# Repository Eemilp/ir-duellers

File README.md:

# IR-duellers

Toy guns for a western-style duelling game. The pair of guns have an ir-LED and sensor each and can thus determine who shot first. When a gun "dies" it is not able to shoot anymore and has to be reset from a button to be functional again. 

A few images of the finished product: https://imgur.com/a/vaQRZun

## Electronics

The heart of the gun is an ATtiny85 with a TSOP312xx (TSOP31236 in this implementation) IR-receiver and an IR-LED. Additionally a status LED and a piezo-buzzer were added for feedback. 

A transistor was also added to amplify the IR-LEDs signal, but in hindsight this was unneccessary. The pizeo-buzzer could however have really done with some amplification, because it can be a bit too quiet sometimes. 

While operational everything runs on two AA batteries, but the design is 5v tolerant for programming purposes.  

The pcb also provides some breakout points for easier programming (VCC, GND, Reset, RX, TX). Unfotunately the internal clockspeed on the ATtiny85 seems to vary so much from chip to chip that it makes programming the chip over serial a hit or miss. Some chips seemed to work perfectly, while others just would not work. Therefore the chips were programmed with SPI. 

## Case

The case was designed in FreeCAD and 3d printed using PLA-plastic. Most parts are attached with screws but the trigger button is just slid in and held in place with friction. Note that the attachment of the top cover is not perfect and I have therefore used tape for fastening it as it's easier. 

The reset switch is a generic closing switch with a 7mm shaft. The trigger is a PS507MA, which is also a closing switch with a 16mm shaft.

------

## Software

Originally the program was written in the Arduino language. While this worked, an improved version was written in assembler. I have also included the version written in the Arduino language here, but be aware that it tends to be somewhat unreliable. Both versions here are programmed to work with 36kHz IR signal. 

Note that this project requires the ATTinyCore by SpenceKonde to be installed from the Arduino boards manager.

## Flashing the chips

The original plan was to program the chip over serial with the Arduino bootloader. This however did not appear to be reliable so programming the chips over SPI on a breadboard was used instead. An Arduino Uno (Arduino as ISP) was used as the programmer.

For the version written in assembler the hex file was generated with Atmel Studio and progamming was done with Avrdude. Avrdude comes with Arduino IDE and can be accessed over command line.

```bash

avrdude -CC:"\Path\to\Arduino\hardware\tools\avr/etc/avrdude.conf" -v -pattiny85 -carduino -PCOM3 -b19200 -U lfuse:w:0xE2:m -U hfuse:w:0xDF:m -U efuse:w:0xFF:m -Uflash:w:lightguns_asm_v1.hex:i

```

I have here the Arduino running Arduino as ISP on COM3. Also note the fuse settings. These set the internal oscillator at 8MHz and make sure that the chip can be programmed again using SPI.

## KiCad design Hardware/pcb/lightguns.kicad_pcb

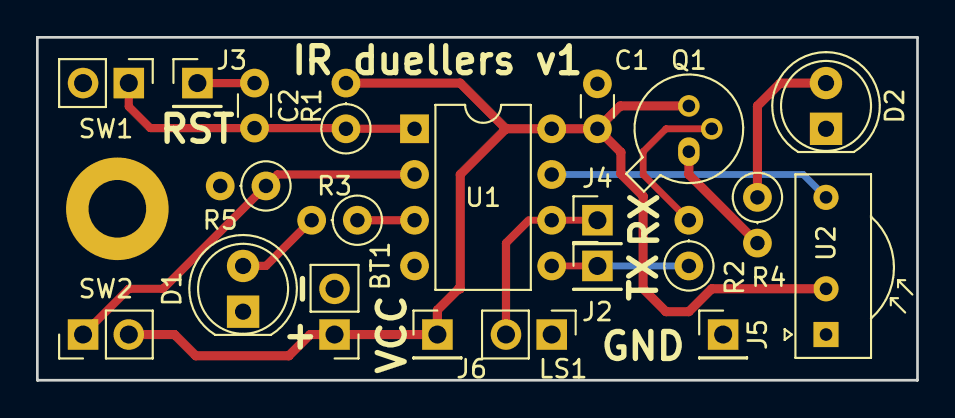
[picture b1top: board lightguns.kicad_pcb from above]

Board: 2 copper layers, 48.9 x 19.1 mm, 21 parts (0 on the bottom side), 13 nets.

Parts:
BT1: Battery; PinHeader_1x02_P2.54mm_Vertical
C1, C2: 0.1uF; C_Disc_D3.0mm_W1.6mm_P2.50mm
D1: LED; LED_D5.0mm_Clear
D2: IR_LED; LED_D5.0mm_IRGrey
J2: TX; PinHeader_1x01_P2.54mm_Vertical
J3: RST; PinHeader_1x01_P2.54mm_Vertical
J4: RX; PinHeader_1x01_P2.54mm_Vertical
J5: GND; PinHeader_1x01_P2.54mm_Vertical
J6: VCC; PinHeader_1x01_P2.54mm_Vertical
LS1: SPKR; PinHeader_1x02_P2.54mm_Vertical
Q1: BC109; TO-18-3
R1, R5: 10k; R_Axial_DIN0207_L6.3mm_D2.5mm_P2.54mm_Vertical
R2: 1k; R_Axial_DIN0207_L6.3mm_D2.5mm_P2.54mm_Vertical
R3: 470; R_Axial_DIN0207_L6.3mm_D2.5mm_P2.54mm_Vertical
R4: 75; R_Axial_DIN0207_L6.3mm_D2.5mm_P2.54mm_Vertical
SW1: RST SW; PinHeader_1x02_P2.54mm_Vertical
SW2: TRIG; PinHeader_1x02_P2.54mm_Vertical
U1: ATtiny85-20PU; DIP-8_W7.62mm
U2: TSOP17xx; Vishay_CAST-3Pin

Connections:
+3V3: BT1.1, C1.1, J6.1, Q1.3, R1.2, SW2.2, U1.8, U2.2
GND: BT1.2, C1.2, D1.1, D2.1, J5.1, LS1.1, R5.2, SW1.2, U1.4, U2.1
unnamed: C2.1, J3.1
unnamed: C2.2, R1.1, SW1.1, U1.1
unnamed: D1.2, R3.2
unnamed: D2.2, R4.1
unnamed: J2.1, R2.1, U1.5
unnamed: J4.1, LS1.2, U1.6
unnamed: Q1.1, R4.2
unnamed: Q1.2, R2.2
unnamed: R3.1, U1.3
unnamed: R5.1, SW2.1, U1.2
unnamed: U1.7, U2.3

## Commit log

2020-12-15 added everything
